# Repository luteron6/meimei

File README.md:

# meimei
A simple, wireless, 75% keyboard! Not too big or small. It runs ZMK.

# Why?
My first exposure to keyboards was through Hack Club's #hackpad, in which I made a 5-key macropad with an encoder and screen. I've never had a regular mechanical keyboard, and this is my attempt at making one. It has a function row, all the necessary keys for typing, and a rotary encoder. Since I mainly use a laptop, I wanted this keyboard to be fully wireless.

## Code - ZMK
After watching many [Joe Scotto](https://www.youtube.com/@joe_scotto) videos, I came to the conclusion that the only reasonable microcontroller to use was the [nice!nano v2](https://nicekeyboards.com/docs/nice-nano/pinout-schematic).

It's suggested to run ZMK as the firmware for bluetooth, so I learned ZMK for this keyboard. Previously I've used QMK, but ZMK is quite different as it uses a Github Actions workflow to compile the firmware file. The firmware for this keyboard lives in [this](https://github.com/luteron6/zmk-config-meimei) repository. Simply go to the [Actions](https://github.com/luteron6/zmk-config-meimei/actions) tab, open the most recent workflow, download the firmware Artifact, unzip the firmware, and flash it to the nice!nano. 

All the source files for ZMK are in the /Code folder in this repository.

## PCB
I made the PCB in KiCad, using [Joe Scotto's symbol/footprint/3D model library](https://github.com/joe-scotto/scottokeebs/tree/main/Extras/ScottoKicad).

It was really helpful as his footprints had 3D models linked to them, because it transferred into Onshape when I worked on my CAD. I included a power button to turn off the keyboard when I travel with it, and an encoder for good measure.

I chose to go with the biggest reasonable battery for this project, so I chose a 3048128 3400mAh battery. According to the [ZMK Power Profiler](https://zmk.dev/power-profiler), this keyboard will last 1 year and 1 month. So basically forever. And ZMK can report battery usage over bluetooth, so this keyboard will literally never die.

The PCB files are in the /PCB folder, including the KiCad source files and the Gerbers for production.

## CAD
As mentioned above, the CAD was made in Onshape. The case has two parts, both of which are in the /CAD folder along with the STEP file of everything. It's meant to be 3D printed and screwed together using threaded inserts and M2 screws.

## BOM
| Item                     | QTY Needed | QTY Purchased | Price   | Description          | Link                                                                                             |
|--------------------------|------------|----|---------|---------------------------------|--------------------------------------------------------------------------------------------------|
| Keyswitches              | 74         | 90 | $27.98  | Clicky switches                 | [Link](https://www.amazon.com/Akko-Keyboard-Diffuser-Mechanical-Structure/dp/B0DJNSK6TD/)        |
| Keycaps (Japanese Maple) |            |    | $25.99  |                                 | [Link](https://www.amazon.com/Japanese-Keycaps-Sublimation-Mechanical-Keyboard/dp/B08Y6S1N3X/)   |
| nice!nano                | 1          | 1  | $24.99  | microcontroller                 | [Link](https://www.littlekeyboards.com/products/nice-nano)                                       |
| PCB                      | 1          | 5  | $30.00  | JLCPCB (also includes shipping) |                                                                                                  |
| diodes                   | 70         | 125 | $5.99  | SOD-123 package diodes          | [Link](https://www.amazon.com/100-Pieces-1N4148W-Switching-High-Speed/dp/B079KJX5J9/)            |
| Stabilizers              |            |    | $18.99  | Spacebar/2u stabilizers         | [Link](https://www.amazon.com/DUROCK-Stabilizers-Translucent-Keyboard-Mechanical/dp/B0B2RVN19F/) |
| peel-away sockets        | 2          | 2  | $6.00   | socketing the microcontroller   | [Link](https://ringerkeys.com/products/peel-a-way-sockets?variant=40212560576594)                |
| peel-away pins           | 2          | 2  | $6.00   | socketing the microcontroller   | [Link](https://ringerkeys.com/products/peel-a-way-sockets?variant=40212560609362)                |
| Battery                  | 1          | 1  | $8.99   | A 3048128 3400mAh battery       | [Link](https://www.amazon.com/YTKavq-3400mAh-Battery-Rechargeable-Connector/dp/B08TTJ79JV/)      |
| Latching Switches        | 1          | 3  | $7.99   | Power on/off switch             | [Link](https://www.amazon.com/Gebildet-Prewired-Waterproof-Self-Locking-Stainless/dp/B0BXPFW69R/) |
| littlekeyboards shipping |            |    | $6.00   |                                 |                                                                                                   |
| ringerkeys shipping      |            |    | $6.00   |                                 |                                                                                                   |
| Total                    |            |    | $174.92 |                                 |                                                                                                   |

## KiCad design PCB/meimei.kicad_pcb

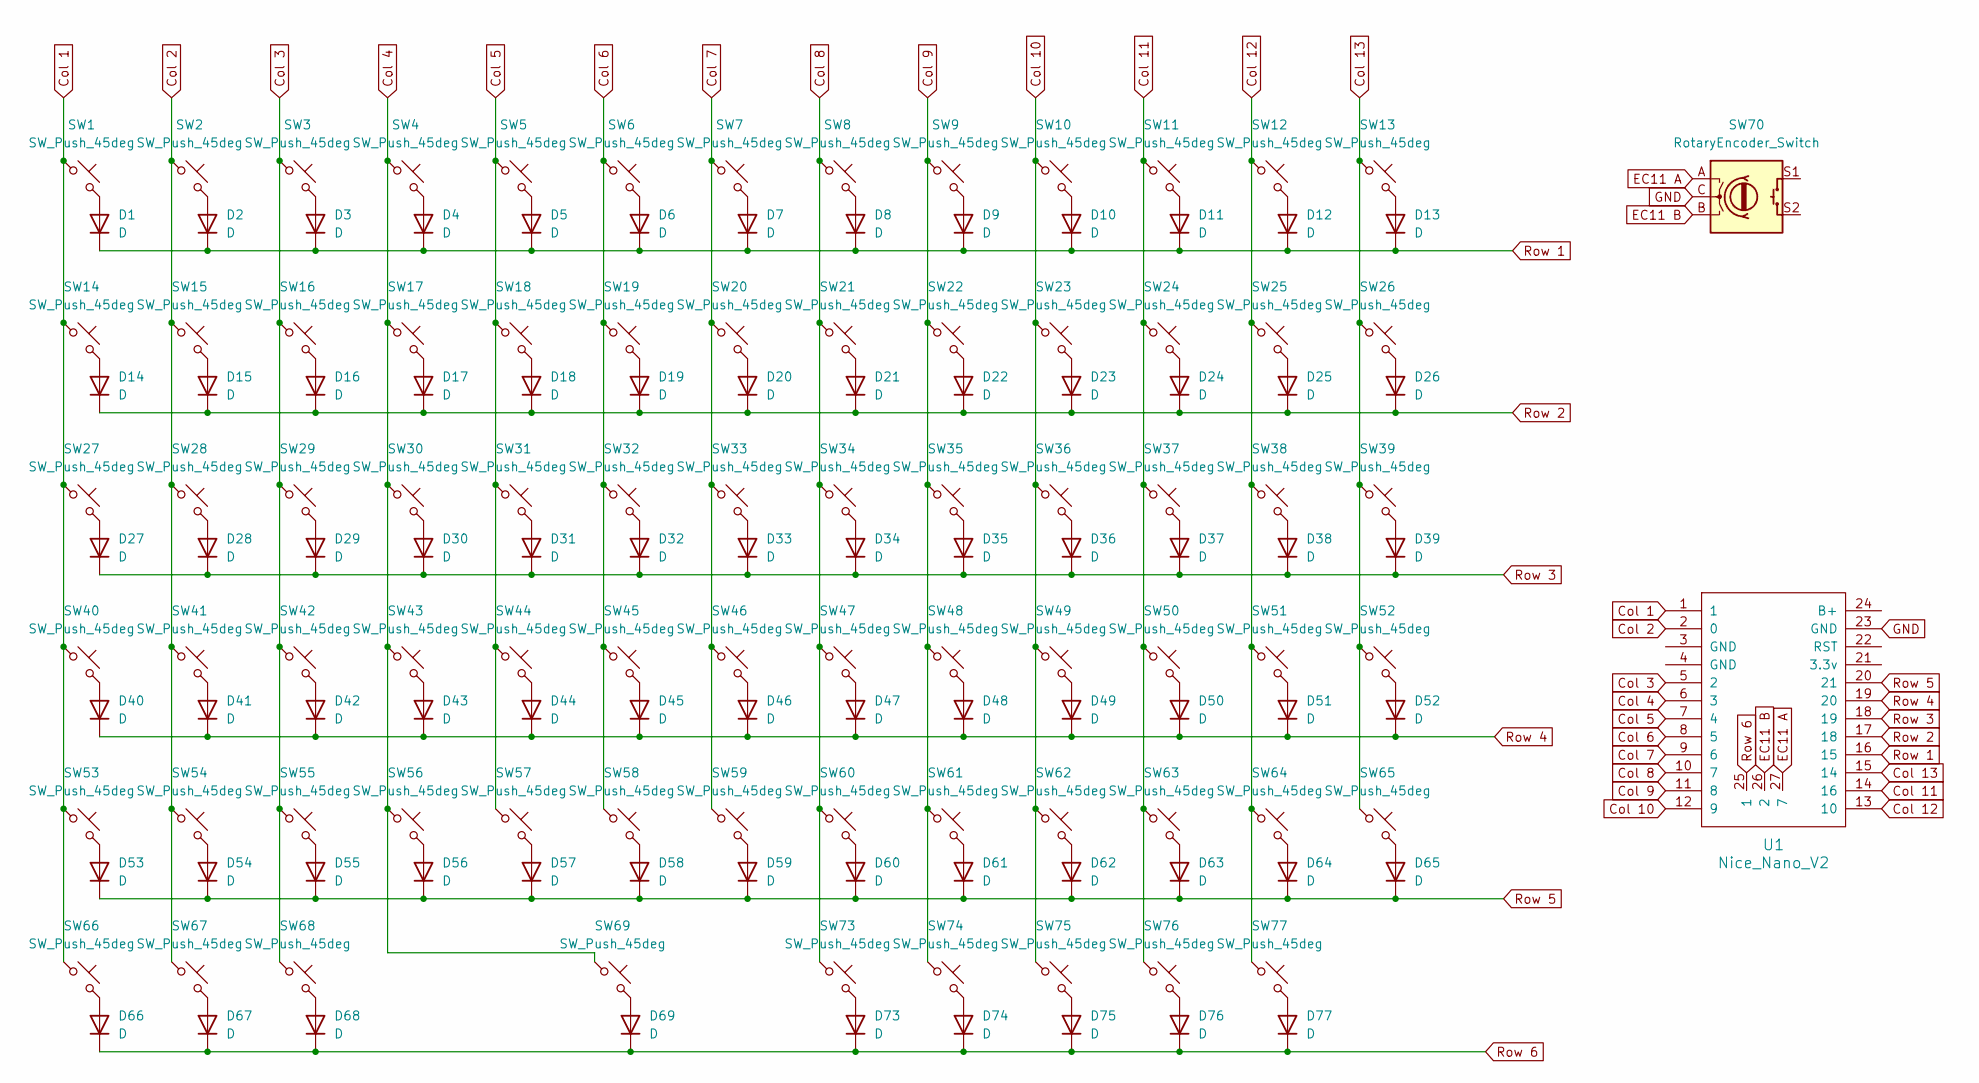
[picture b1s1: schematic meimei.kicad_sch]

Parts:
D1, D2, D3, D4, D5, D6, D7, D8, D9, D10, D11, D12, D13, D14, D15, D16, D17, D18, D19, D20, D21, D22, D23, D24, D25, D26, D27, D28, D29, D30, D31, D32, D33, D34, D35, D36, D37, D38, D39, D40, D41, D42, D43, D44, D45, D46, D47, D48, D49, D50, D51, D52, D53, D54, D55, D56, D57, D58, D59, D60, D61, D62, D63, D64, D65, D66, D67, D68, D69, D73, D74, D75, D76, D77: D; D_SOD-123
SW1, SW2, SW3, SW4, SW5, SW6, SW7, SW8, SW9, SW10, SW11, SW12, SW13, SW14, SW15, SW16, SW17, SW18, SW19, SW20, SW21, SW22, SW23, SW24, SW25, SW26, SW28, SW29, SW30, SW31, SW32, SW33, SW34, SW35, SW36, SW37, SW38, SW39, SW41, SW42, SW43, SW44, SW45, SW46, SW47, SW48, SW49, SW50, SW51, SW54, SW55, SW56, SW57, SW58, SW59, SW60, SW61, SW62, SW63: SW_Push_45deg; MX_PCB_1.00u
SW27, SW52: SW_Push_45deg; MX_PCB_1.50u
SW40: SW_Push_45deg; MX_PCB_1.75u
SW53, SW64: SW_Push_45deg; MX_PCB_2.25u
SW65: SW_Push_45deg; MX_PCB_2.00u
SW66, SW67, SW68, SW73, SW74, SW75, SW76: SW_Push_45deg; MX_PCB_1.25u
SW69: SW_Push_45deg; MX_PCB_6.25u
SW70: RotaryEncoder_Switch; Encoder_EC11_MX
SW77: SW_Push_45deg; MX_PCB_2.75u
U1: Nice_Nano_V2

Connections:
Col 1: SW1.1, SW14.1, SW27.1, SW40.1, SW53.1, SW66.1, U1.1
Col 2: SW2.1, SW15.1, SW28.1, SW41.1, SW54.1, SW67.1, U1.2 (0)
Col 3: SW3.1, SW16.1, SW29.1, SW42.1, SW55.1, SW68.1, U1.5 (2)
Col 4: SW4.1, SW17.1, SW30.1, SW43.1, SW56.1, SW69.1, U1.6 (3)
Col 5: SW5.1, SW18.1, SW31.1, SW44.1, SW57.1, U1.7 (4)
Col 6: SW6.1, SW19.1, SW32.1, SW45.1, SW58.1, U1.8 (5)
Col 7: SW7.1, SW20.1, SW33.1, SW46.1, SW59.1, U1.9 (6)
Col 8: SW8.1, SW21.1, SW34.1, SW47.1, SW60.1, SW73.1, U1.10 (7)
Col 9: SW9.1, SW22.1, SW35.1, SW48.1, SW61.1, SW74.1, U1.11 (8)
Col 10: SW10.1, SW23.1, SW36.1, SW49.1, SW62.1, SW75.1, U1.12 (9)
Col 11: SW11.1, SW24.1, SW37.1, SW50.1, SW63.1, SW76.1, U1.14 (16)
Col 12: SW12.1, SW25.1, SW38.1, SW51.1, SW64.1, SW77.1, U1.13 (10)
Col 13: SW13.1, SW26.1, SW39.1, SW52.1, SW65.1, U1.15 (14)
EC11 A: SW70.A, U1.27 (7)
EC11 B: SW70.B, U1.26 (2)
GND: SW70.C, U1.23 (GND)
unnamed: D1.2 (A), SW1.2
unnamed: D2.2 (A), SW2.2
unnamed: D3.2 (A), SW3.2
unnamed: D4.2 (A), SW4.2
unnamed: D5.2 (A), SW5.2
unnamed: D6.2 (A), SW6.2
unnamed: D7.2 (A), SW7.2
unnamed: D8.2 (A), SW8.2
unnamed: D9.2 (A), SW9.2
unnamed: D10.2 (A), SW10.2
unnamed: D11.2 (A), SW11.2
unnamed: D12.2 (A), SW12.2
unnamed: D13.2 (A), SW13.2
unnamed: D14.2 (A), SW14.2
unnamed: D15.2 (A), SW15.2
unnamed: D16.2 (A), SW16.2
unnamed: D17.2 (A), SW17.2
unnamed: D18.2 (A), SW18.2
unnamed: D19.2 (A), SW19.2
unnamed: D20.2 (A), SW20.2
unnamed: D21.2 (A), SW21.2
unnamed: D22.2 (A), SW22.2
unnamed: D23.2 (A), SW23.2
unnamed: D24.2 (A), SW24.2
unnamed: D25.2 (A), SW25.2
unnamed: D26.2 (A), SW26.2
unnamed: D27.2 (A), SW27.2
unnamed: D28.2 (A), SW28.2
unnamed: D29.2 (A), SW29.2
unnamed: D30.2 (A), SW30.2
unnamed: D31.2 (A), SW31.2
unnamed: D32.2 (A), SW32.2
unnamed: D33.2 (A), SW33.2
unnamed: D34.2 (A), SW34.2
unnamed: D35.2 (A), SW35.2
unnamed: D36.2 (A), SW36.2
unnamed: D37.2 (A), SW37.2
unnamed: D38.2 (A), SW38.2
unnamed: D39.2 (A), SW39.2
unnamed: D40.2 (A), SW40.2
unnamed: D41.2 (A), SW41.2
unnamed: D42.2 (A), SW42.2
unnamed: D43.2 (A), SW43.2
unnamed: D44.2 (A), SW44.2
unnamed: D45.2 (A), SW45.2
unnamed: D46.2 (A), SW46.2
unnamed: D47.2 (A), SW47.2
unnamed: D48.2 (A), SW48.2
unnamed: D49.2 (A), SW49.2
unnamed: D50.2 (A), SW50.2
unnamed: D51.2 (A), SW51.2
unnamed: D52.2 (A), SW52.2
unnamed: D53.2 (A), SW53.2
unnamed: D54.2 (A), SW54.2
unnamed: D55.2 (A), SW55.2
unnamed: D56.2 (A), SW56.2
unnamed: D57.2 (A), SW57.2
unnamed: D58.2 (A), SW58.2
unnamed: D59.2 (A), SW59.2
unnamed: D60.2 (A), SW60.2
unnamed: D61.2 (A), SW61.2
unnamed: D62.2 (A), SW62.2
unnamed: D63.2 (A), SW63.2
unnamed: D64.2 (A), SW64.2
unnamed: D65.2 (A), SW65.2
unnamed: D66.2 (A), SW66.2
unnamed: D67.2 (A), SW67.2
unnamed: D68.2 (A), SW68.2
unnamed: D69.2 (A), SW69.2
unnamed: D73.2 (A), SW73.2
unnamed: D74.2 (A), SW74.2
unnamed: D75.2 (A), SW75.2
unnamed: D76.2 (A), SW76.2
unnamed: D77.2 (A), SW77.2
Row 1: D1.1 (K), D2.1 (K), D3.1 (K), D4.1 (K), D5.1 (K), D6.1 (K), D7.1 (K), D8.1 (K), D9.1 (K), D10.1 (K), D11.1 (K), D12.1 (K), D13.1 (K), U1.16 (15)
Row 2: D14.1 (K), D15.1 (K), D16.1 (K), D17.1 (K), D18.1 (K), D19.1 (K), D20.1 (K), D21.1 (K), D22.1 (K), D23.1 (K), D24.1 (K), D25.1 (K), D26.1 (K), U1.17 (18)
Row 3: D27.1 (K), D28.1 (K), D29.1 (K), D30.1 (K), D31.1 (K), D32.1 (K), D33.1 (K), D34.1 (K), D35.1 (K), D36.1 (K), D37.1 (K), D38.1 (K), D39.1 (K), U1.18 (19)
Row 4: D40.1 (K), D41.1 (K), D42.1 (K), D43.1 (K), D44.1 (K), D45.1 (K), D46.1 (K), D47.1 (K), D48.1 (K), D49.1 (K), D50.1 (K), D51.1 (K), D52.1 (K), U1.19 (20)
Row 5: D53.1 (K), D54.1 (K), D55.1 (K), D56.1 (K), D57.1 (K), D58.1 (K), D59.1 (K), D60.1 (K), D61.1 (K), D62.1 (K), D63.1 (K), D64.1 (K), D65.1 (K), U1.20 (21)
Row 6: D66.1 (K), D67.1 (K), D68.1 (K), D69.1 (K), D73.1 (K), D74.1 (K), D75.1 (K), D76.1 (K), D77.1 (K), U1.25 (1)

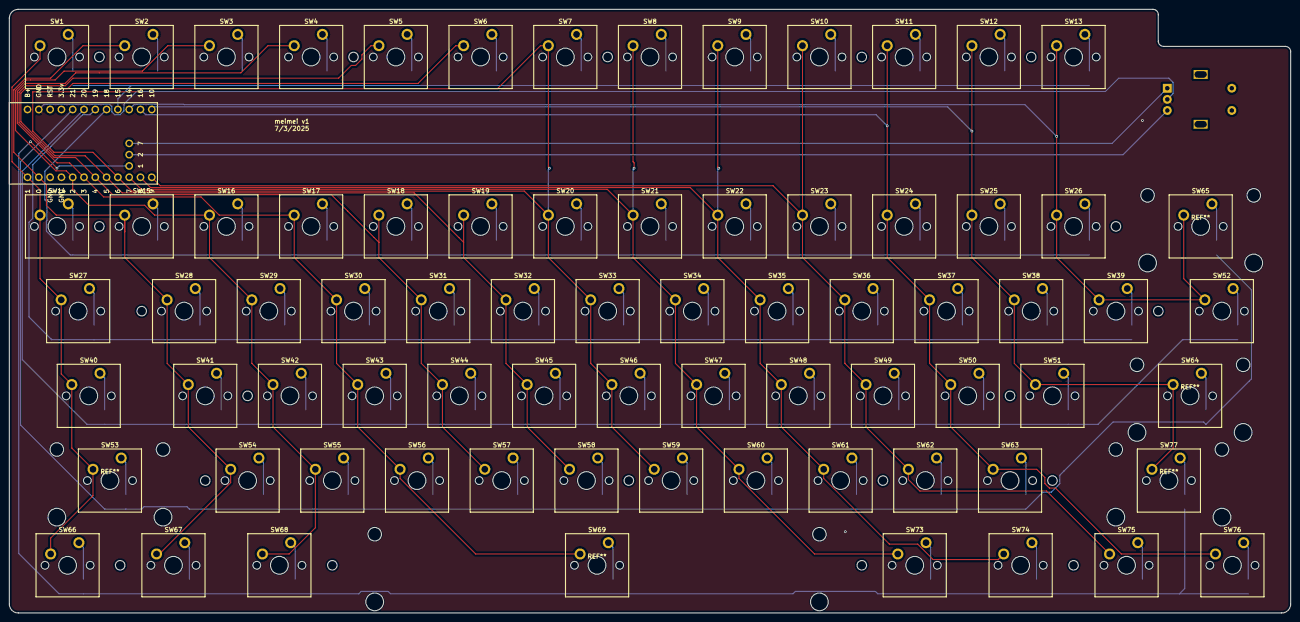
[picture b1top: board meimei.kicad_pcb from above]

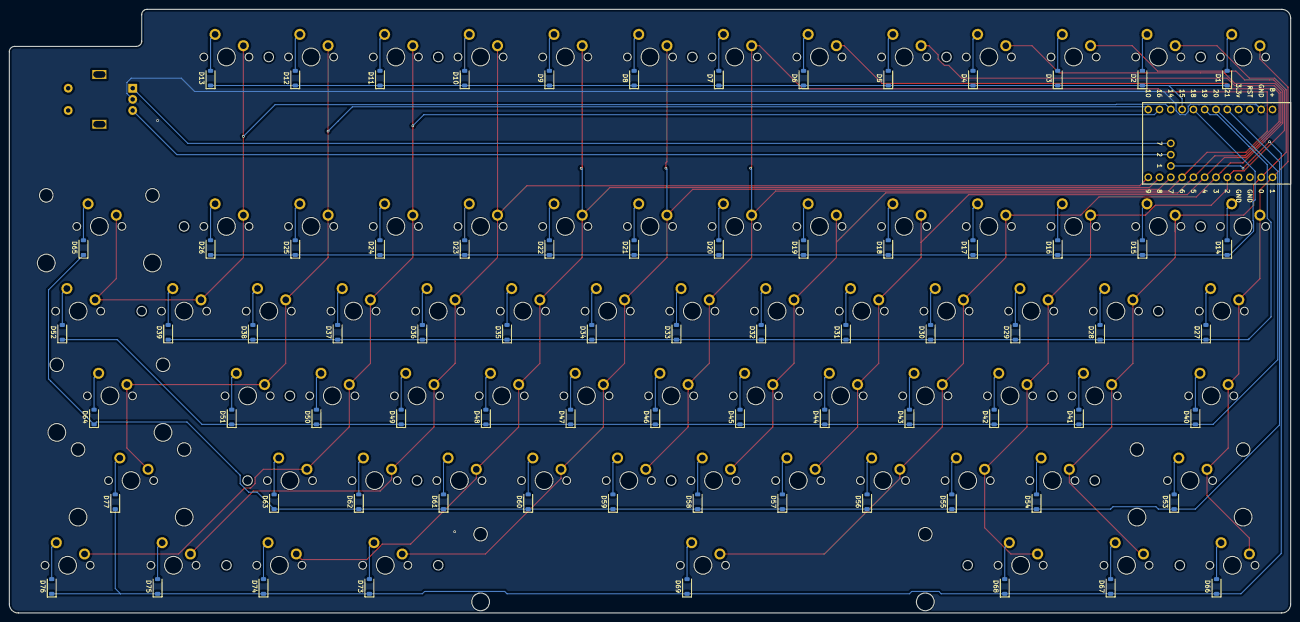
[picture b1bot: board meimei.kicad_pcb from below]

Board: 2 copper layers, 288.1 x 135.7 mm, 150 parts (74 on the bottom side), 96 nets.

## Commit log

2025-06-21 Day 1!
2025-07-03 Day 2!
2025-07-03 Day 3!
2025-07-05 fixed headers
2025-07-05 All source and production files and README
    missing the CAD STEP file
2025-07-05 Added STEP file
    GH says STEP file with PCB is too big to upload
2025-08-19 Day 6
